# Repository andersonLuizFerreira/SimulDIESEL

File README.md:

# SimulDIESEL

---

# Português

O SimulDIESEL consiste em uma plataforma de bancada destinada à manutenção, diagnóstico, análise, simulação e validação de centrais e módulos automotivos da linha DIESEL, com foco em caminhões, máquinas agrícolas e equipamentos pesados.

Suas ferramentas permitem ao reparador realizar testes, simulações e análises de funcionamento de redes, sinais e módulos eletrônicos, auxiliando processos de manutenção, desenvolvimento, engenharia reversa e diagnóstico avançado em bancada.

Para conhecer mais sobre o projeto, leia:

- [`docs/README.md`](docs/README.md)
- [`docs/00-INDICE.md`](docs/00-INDICE.md)

Esses arquivos guiarão você pela documentação e estrutura do projeto.

## agentes de IA

Siga para:

- [`.agents/README.md`](.agents/README.md)

---

# English

SimulDIESEL is a bench platform designed for maintenance, diagnostics, analysis, simulation, and validation of DIESEL automotive control units and electronic modules, focused on trucks, agricultural machines, and heavy equipment.

Its tools allow technicians to perform tests, simulations, and analysis of networks, signals, and electronic modules, supporting maintenance, development, reverse engineering, and advanced bench diagnostics.

To learn more about the project, read:

- [`docs/README.md`](docs/README.md)
- [`docs/00-INDICE.md`](docs/00-INDICE.md)

These files will guide you through the project's documentation and structure.

## AI agents

Proceed to:

- [`.agents/README.md`](.agents/README.md)

---

# Español

SimulDIESEL es una plataforma de banco destinada al mantenimiento, diagnóstico, análisis, simulación y validación de centrales y módulos automotrices de la línea DIESEL, enfocada en camiones, maquinaria agrícola y equipos pesados.

Sus herramientas permiten al reparador realizar pruebas, simulaciones y análisis del funcionamiento de redes, señales y módulos electrónicos, ayudando en procesos de mantenimiento, desarrollo, ingeniería inversa y diagnóstico avanzado en banco.

Para conocer más sobre el proyecto, lea:

- [`docs/README.md`](docs/README.md)
- [`docs/00-INDICE.md`](docs/00-INDICE.md)

Estos archivos lo guiarán a través de la documentación y estructura del proyecto.

## agentes de IA

Diríjase a:

- [`.agents/README.md`](.agents/README.md)

---

# Deutsch

SimulDIESEL ist eine Prüfstandsplattform für Wartung, Diagnose, Analyse, Simulation und Validierung von Steuergeräten und elektronischen Modulen im DIESEL-Bereich mit Fokus auf Lastkraftwagen, landwirtschaftliche Maschinen und schwere Geräte.

Die Werkzeuge ermöglichen Technikern die Durchführung von Tests, Simulationen und Analysen von Netzwerken, Signalen und elektronischen Modulen und unterstützen Wartung, Entwicklung, Reverse Engineering und erweiterte Prüfstandsdiagnosen.

Um mehr über das Projekt zu erfahren, lesen Sie:

- [`docs/README.md`](docs/README.md)
- [`docs/00-INDICE.md`](docs/00-INDICE.md)

Diese Dateien führen Sie durch die Dokumentation und Struktur des Projekts.

## KI-Agenten

Weiter zu:

- [`.agents/README.md`](.agents/README.md)

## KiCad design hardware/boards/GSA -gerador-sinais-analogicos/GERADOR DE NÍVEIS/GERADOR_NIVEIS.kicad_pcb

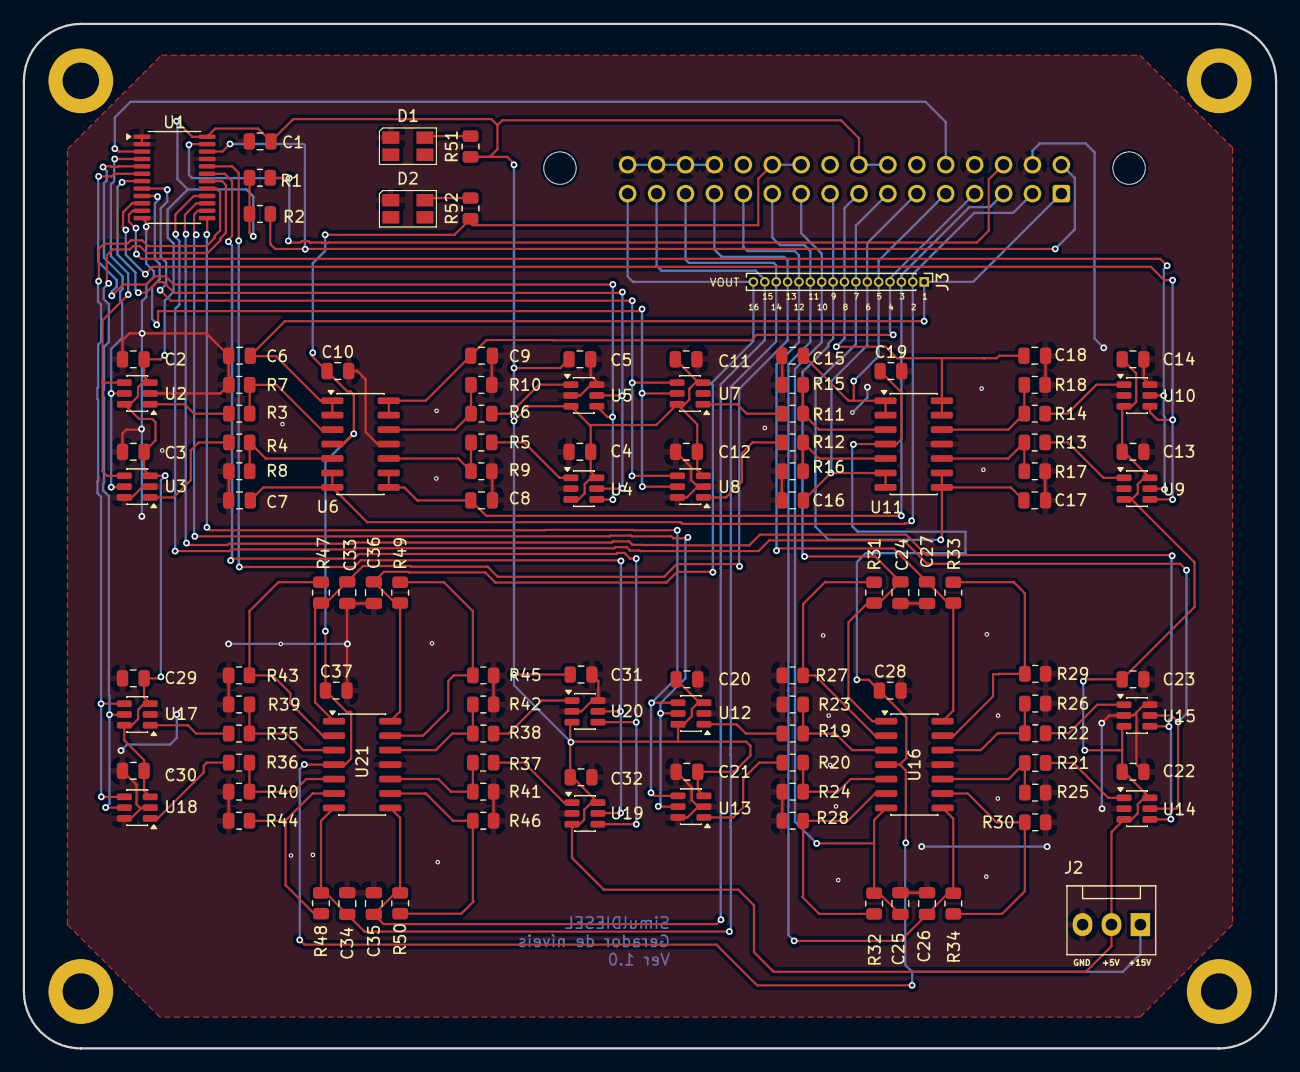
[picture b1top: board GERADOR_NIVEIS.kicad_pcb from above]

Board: 2 copper layers, 110.0 x 90.0 mm, 115 parts (1 on the bottom side), 80 nets.

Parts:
C1, C2, C3, C4, C5, C6, C7, C8, C9, C10, C11, C12, C13, C14, C15, C16, C17, C18, C19, C20, C21, C22, C23, C24, C25, C26, C27, C28, C29, C30, C31, C32, C33, C34, C35, C36, C37: 100nF; C_0805_2012Metric
D1, D2: LED; LED_Avago_PLCC4_3.2x2.8mm_CW
J1: DIN41612_02x16_AB; DIN41612_B2_2x16_Female_Vertical_THT
J2: Conn_01x03_Pin; FanPinHeader_1x03_P2.54mm_Vertical
J3: Conn_01x16_Pin; PinHeader_1x16_P1.00mm_Vertical
R1, R2: 4K7; R_0805_2012Metric
R3, R4, R5, R6, R11, R12, R13, R14, R19, R20, R21, R22, R35, R36, R37, R38, R51: 1K; R_0805_2012Metric
R7, R8, R9, R10, R15, R16, R17, R18, R23, R24, R25, R26, R39, R40, R41, R42: 100K; R_0805_2012Metric
R27, R28, R29, R30, R43, R44, R45, R46: 10K; R_0805_2012Metric
R31, R32, R33, R34, R47, R48, R49, R50: 15K; R_0805_2012Metric
R52: 3k3; R_0805_2012Metric
U1: TCA9548APWR; TSSOP-24_4.4x7.8mm_P0.65mm
U2, U3, U4, U5, U7, U8, U9, U10, U12, U13, U14, U15, U17, U18, U19, U20: MCP4725AOT; SOT-23-6
U6, U11, U16, U21: LM2902; SOIC-14_3.9x8.7mm_P1.27mm

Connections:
+15V: C10.1, C19.1, C28.1, C37.1, J1.b10, J1.b11, J2.1, R52.1, U6.4 (V+), U11.4 (V+), U16.4 (V+), U21.4 (V+)
/SC0: U1.5 (SC0), U2.5 (SCL), U3.5 (SCL)
/SC1: U1.7 (SC1), U4.5 (SCL), U5.5 (SCL)
/SC2: U1.9 (SC2), U7.5 (SCL), U8.5 (SCL)
/SC3: U1.11 (SC3), U9.5 (SCL), U10.5 (SCL)
/SC4: U1.14 (SC4), U12.5 (SCL), U13.5 (SCL)
/SC5: U1.16 (SC5), U14.5 (SCL), U15.5 (SCL)
/SC6: U1.18 (SC6), U17.5 (SCL), U18.5 (SCL)
/SC7: U1.20 (SC7), U19.5 (SCL), U20.5 (SCL)
/SCL: J1.b1, R2.2, U1.22 (SCL)
/SD0: U1.4 (SD0), U2.4 (SDA), U3.4 (SDA)
/SD1: U1.6 (SD1), U4.4 (SDA), U5.4 (SDA)
/SD2: U1.8 (SD2), U7.4 (SDA), U8.4 (SDA)
/SD3: U1.10 (SD3), U9.4 (SDA), U10.4 (SDA)
/SD4: U1.13 (SD4), U12.4 (SDA), U13.4 (SDA)
/SD5: U1.15 (SD5), U14.4 (SDA), U15.4 (SDA)
/SD6: U1.17 (SD6), U17.4 (SDA), U18.4 (SDA)
/SD7: U1.19 (SD7), U19.4 (SDA), U20.4 (SDA)
/SDA: J1.b3, R1.2, U1.23 (SDA)
/VOUT1: C6.1, J1.a1, J3.1, U6.1, U6.2 (-)
/VOUT2: C7.1, J1.a2, J3.2, U6.6 (-), U6.7
/VOUT3: C8.1, J1.a3, J3.3, U6.8, U6.9 (-)
/VOUT4: C9.1, J1.a4, J3.4, U6.13 (-), U6.14
/VOUT5: C15.1, J1.a5, J3.5, U11.1, U11.2 (-)
/VOUT6: C16.1, J1.a6, J3.6, U11.6 (-), U11.7
/VOUT7: C17.1, J1.a7, J3.7, U11.8, U11.9 (-)
/VOUT8: C18.1, J1.a8, J3.8, U11.13 (-), U11.14
/VOUT9: C24.1, J1.a9, J3.9, R31.2, U16.1
/VOUT10: C25.1, J1.a10, J3.10, R32.2, U16.7
/VOUT11: C26.1, J1.a11, J3.11, R34.2, U16.8
/VOUT12: C27.1, J1.a12, J3.12, R33.2, U16.14
/VOUT13: C33.1, J1.a13, J3.13, R47.2, U21.1
/VOUT14: C34.1, J1.a14, J3.14, R48.2, U21.7
/VOUT15: C35.1, J1.a15, J3.15, R50.2, U21.8
/VOUT16: C36.1, J1.a16, J3.16, R49.2, U21.14
/~RST: J1.b5, U1.3 (~RESET)
GND: C1.1, C2.2, C3.2, C4.2, C5.2, C6.2, C7.2, C8.2, C9.2, C10.2, C11.2, C12.2, C13.2, C14.2, C15.2, C16.2, C17.2, C18.2, C19.2, C20.2, C21.2, C22.2, C23.2, C24.2, C25.2, C26.2, C27.2, C28.2, C29.2, C30.2, C31.2, C32.2, C33.2, C34.2, C35.2, C36.2, C37.2, D1.1 (K), D2.1 (K), J1.b2, J1.b4, J1.b13, J1.b14, J1.b15, J1.b16, J2.3, R7.1, R8.1, R9.1, R10.1, R15.1, R16.1, R17.1, R18.1, R23.1, R24.1, R25.1, R26.1, R27.1, R28.1, R29.1, R30.1, R39.1, R40.1, R41.1, R42.1, R43.1, R44.1, R45.1, R46.1, U1.1 (A0), U1.2 (A1), U1.12 (GND), U1.21 (A2), U2.2 (VSS), U3.2 (VSS), U3.6 (A0), U4.2 (VSS), U5.2 (VSS), U5.6 (A0), U6.11 (V-), U7.2 (VSS), U8.2 (VSS), U8.6 (A0), U9.2 (VSS), U10.2 (VSS), U10.6 (A0), U11.11 (V-), U12.2 (VSS), U13.2 (VSS), U13.6 (A0), U14.2 (VSS), U15.2 (VSS), U15.6 (A0), U16.11 (V-), U17.2 (VSS), U18.2 (VSS), U18.6 (A0), U19.2 (VSS), U20.2 (VSS), U20.6 (A0), U21.11 (V-)
unnamed: D1.2 (A), R51.2
unnamed: D2.2 (A), R52.2
unnamed: R3.1, U2.1 (VOUT)
unnamed: R4.1, U3.1 (VOUT)
unnamed: R5.1, U4.1 (VOUT)
unnamed: R6.1, U5.1 (VOUT)
unnamed: R3.2, R7.2, U6.3 (+)
unnamed: R4.2, R8.2, U6.5 (+)
unnamed: R5.2, R9.2, U6.10 (+)
unnamed: R6.2, R10.2, U6.12 (+)
unnamed: R11.1, U7.1 (VOUT)
unnamed: R12.1, U8.1 (VOUT)
unnamed: R13.1, U9.1 (VOUT)
unnamed: R14.1, U10.1 (VOUT)
unnamed: R11.2, R15.2, U11.3 (+)
unnamed: R12.2, R16.2, U11.5 (+)
unnamed: R13.2, R17.2, U11.10 (+)
unnamed: R14.2, R18.2, U11.12 (+)
unnamed: R19.1, U12.1 (VOUT)
unnamed: R20.1, U13.1 (VOUT)
unnamed: R21.1, U14.1 (VOUT)
unnamed: R22.1, U15.1 (VOUT)
unnamed: R19.2, R23.2, U16.3 (+)
unnamed: R27.2, R31.1, U16.2 (-)
unnamed: R20.2, R24.2, U16.5 (+)
unnamed: R28.2, R32.1, U16.6 (-)
unnamed: R21.2, R25.2, U16.10 (+)
unnamed: R30.2, R34.1, U16.9 (-)
unnamed: R22.2, R26.2, U16.12 (+)
unnamed: R29.2, R33.1, U16.13 (-)
unnamed: R35.1, U17.1 (VOUT)
unnamed: R36.1, U18.1 (VOUT)
unnamed: R37.1, U19.1 (VOUT)
unnamed: R38.1, U20.1 (VOUT)
unnamed: R35.2, R39.2, U21.3 (+)
unnamed: R43.2, R47.1, U21.2 (-)
unnamed: R36.2, R40.2, U21.5 (+)
unnamed: R44.2, R48.1, U21.6 (-)
unnamed: R37.2, R41.2, U21.10 (+)
unnamed: R46.2, R50.1, U21.9 (-)
unnamed: R38.2, R42.2, U21.12 (+)
unnamed: R45.2, R49.1, U21.13 (-)
VCC: C1.2, C2.1, C3.1, C4.1, C5.1, C11.1, C12.1, C13.1, C14.1, C20.1, C21.1, C22.1, C23.1, C29.1, C30.1, C31.1, C32.1, J1.b7, J1.b8, J2.2, R1.1, R2.1, R51.1, U1.24 (VCC), U2.3 (VDD), U2.6 (A0), U3.3 (VDD), U4.3 (VDD), U4.6 (A0), U5.3 (VDD), U7.3 (VDD), U7.6 (A0), U8.3 (VDD), U9.3 (VDD), U9.6 (A0), U10.3 (VDD), U12.3 (VDD), U12.6 (A0), U13.3 (VDD), U14.3 (VDD), U14.6 (A0), U15.3 (VDD), U17.3 (VDD), U17.6 (A0), U18.3 (VDD), U19.3 (VDD), U19.6 (A0), U20.3 (VDD)

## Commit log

2026-02-01 Estruturação das pastas
2026-02-02 docs(protocol): add SD-GW-LINK spec, ADR-0007 and hex test vectors
2026-02-06 Atualização da documentação do protocolo SGGW
2026-02-09 Conexão serial pronta.
2026-02-09 docs: add architecture overview, serial baseline and technical roadmap
2026-02-09 feat: add link handshake...
2026-02-10 Inclusão do novo script git
2026-02-10 Novo script git
2026-02-10 Alteracao no script git
2026-02-10 Alteracoes no scritp do gitlab
2026-02-10 Tratamento de link
2026-02-13 SGGW em desenvolvimento
2026-02-14 Implement stable link handshake, health supervision, and graceful disconnect
2026-02-17 Integrate SGGW: link engine + client API + LED tool + ESP32 firmware
2026-02-21 gateway: reorganiza estrutura para modelo src/ + roteamento TLV puro
2026-02-21 ci: adiciona pipeline placeholder (YAML válido)
2026-02-28 Reestrutura docs e firmware (nova arvore)
2026-02-28 Adiciona CI para firmware (PlatformIO)
2026-02-28 Padroniza estrutura de docs (INDEX, duplicados e Master Spec)
2026-02-28 Adiciona relatório de auditoria estrutural
2026-02-28 Docs: restaura ADR-0007 (COBS + CRC-8)
2026-02-28 Docs: transforma README em HUB técnico
2026-02-28 Docs: adiciona MASTER_SPEC consolidado
2026-02-28 Docs: remove duplicidade de README (SGGW_OVERVIEW, EXAMPLES)
2026-02-28 Docs: ignore auditoria gerada (AUDITORIA_DOCS.md)
2026-02-28 Chore: move relatórios gerados para tools/out e ignora a pasta
2026-03-01 Docs(GSA): adiciona documentação base do firmware (README, protocolo, pinout, fluxo)
2026-03-01 Docs: remove specs do README e normaliza UTF-8
2026-03-01 docs(sggw): freeze SGGW v1.0 (name + ACK/ERR + boundaries)
2026-03-01 docs: add AI workflow + codex instructions
2026-03-06 SimulDIESEL v0.3.0
    Arquitetura estabilizada
    Reorganização completa da documentação
    Separação arquitetura / hardware
    Integração PC ↔ Gateway definida
    Estrutura do projeto consolidada
2026-03-14 docs: restore and sanitize documentation structure
2026-03-14 git: normalize line endings policy
2026-03-14 docs: update documentation and project state
2026-03-16 Fix I2C instability, restore stable BPM/GSA modules, and validate GSA LED command end-to-end
2026-03-17 Refatora arquitetura do local-api por boards, forms logic e camadas de protocolo
2026-03-17 Remove dump técnico da refatoração
2026-03-17 Ajusta regras de EOL no repositório
2026-03-18 docs: atualiza arquitetura oficial host <-> BPM, remove topologia legacy e alinha keepalive por atividade SDGW válida
2026-03-18 refactor: centraliza TX SDGW com scheduler por prioridade, substitui health service por link supervisor e alinha BPM ao keepalive por atividade válida
2026-03-22 Checkpoint antes da implementação completa da GSA
2026-03-22 Implementa expansão SDH/TLV da GSA no host
2026-03-22 Atualiza documentação da GSA e do contrato SDH/TLV
2026-03-22 Remove legados e consolida arquitetura atual da GSA
2026-03-22 Checkpoint antes da migração do TLV 0x12 para 0x1B na GSA
2026-03-22 Migra GSA channel.status de 0x12 para 0x1B
2026-03-22 Checkpoint antes da implementação do firmware GSA com simulação analógica e EEPROM
2026-03-22 Checkpoint antes da implementação I2C real TCA9548 + MCP4725
2026-03-22 Checkpoint antes da implementação da máquina operacional GSA BUSY/IDLE + I2C master/slave + TCA9548 + MCP4725
2026-03-22 Checkpoint antes da integração da UI da GSA com comandos reais
2026-03-24 Checkpoint antes da adaptação do gateway BPM para IRQ + evento 0x31 da GSA
2026-03-24 Checkpoint antes da integração I2C duplo + IRQ + evento 0x31 na GSA
2026-03-24 Checkpoint antes da atualização documental da nova arquitetura GSA/BPM/API
2026-03-24 Checkpoint antes da adaptação da API/UI ao evento 0x31 da GSA
2026-03-27 Checkpoint antes da Fase 1 - refatoracao do host para multiplos transportes
2026-03-27 Refatora host SDGW para desacoplar sessao do transporte e preservar Serial
2026-03-27 Checkpoint antes da Fase 2 - refatoracao do firmware BPM para multiplos transportes
2026-03-27 Refatora firmware BPM para desacoplar SGGW do stream fisico e preservar Serial
2026-03-27 Checkpoint antes da Fase 3 - implementacao Bluetooth host e firmware BPM
2026-03-27 Implementa Bluetooth no host e na BPM com sessao unica e Serial preservada
2026-04-03 Correção definitiva da pinagem BPM-GSA e saneamento global do projeto
2026-04-03 Checkpoint antes da reestruturacao da documentacao
2026-04-05 docs: consolida a árvore oficial da documentação
    Reestrutura a navegação hierárquica, ajusta a conformidade entre pai e filho e organiza a leitura progressiva por camadas.
2026-04-06 docs: aprofunda documentação de firmware e hardware e fecha etapa atual
    Reflete o estado implementado de BPM, GSA e da bancada, consolida as trilhas ONDE e COMO fora da API e registra o fechamento da etapa atual, deixando apenas a finalização da GSA pendente e preparando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
2026-04-06 refactor: consolida nova fundação SDGW e estrutura modular da solução
2026-04-12 feat: comissionamento final e documentacao da UCE
2026-04-17 Checkpoint SPI Parte A: correção do transporte BPM<->UCE com TX explícito no slave, validação de header no master e melhoria na classificação de erros. Builds OK (UCE/BPM). Validação em bancada pende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
2026-04-17 Checkpoint SPI Parte A + comissionamento: correção do transporte BPM<->UCE, dumps técnicos versionados para rastreabilidade, builds OK, validação de bancada pendente
2026-04-24 Commission validated BPM-UCE SPI LED handshake
2026-04-25 feat: comissiona transporte SPI e dispatchers por board
2026-04-25 refactor: centraliza transacoes TLV por board na API
2026-04-25 feat(uce): adiciona CanService logico (0x20-0x23) integrado com dispatcher e API
2026-04-25 Desenvolvendo controle de mensagens CAN
2026-04-27 feat(can): implementa CAN_RX_EVENT assíncrono com pipeline UCE→BPM→API validado em bancada
2026-04-30 Construção de CanService na UCE
2026-04-30 Implantacao da CanService
2026-05-02 Continuação da construção do canService
2026-05-08 feat(can-rx): consolida arquitetura RX AUTO/DIRECT_ONLY com TIC, DATA_MASK e OutputBuffer
    Consolida a ETAPA 10 do fluxo CAN RX com CAN_TIC 0x46, CAN_EDIT otimizado por DATA_MASK e replay oficial via CanRxOutputBuffer.
    Preserva DIRECT_ONLY e CAN_RX_EVENT 0x28, mantém fallback TABLE_FULL, DELETE por timeout, recuperação MIRROR_OUT_OF_SYNC e diagnóstico de FIFO dispatcher.
    Inclui cenários controlados no CanDriver_fake para TIC sem alteração, EDIT com um byte alterado e DELETE por timeout, sem alterar CanDriver real.
2026-05-08 feat(can-tx): valida arquitetura TX DIRECT/TABLE com loopback fake RX/TX
    - implementa CAN_TX_DIRECT/TX_CREATE/TX_EDIT/TX_DELETE
    - adiciona tabela TX na UCE
    - adiciona CanTxManager na API
    - valida loopback TX->RX via CanDriver_fake
    - valida DIRECT_ONLY vs AUTO
    - consolida arquitetura RX/TX da ETAPA 10
2026-05-09 feat(sdctp): consolida arquitetura final CAN transport protocol para producao
2026-05-09 feat(api): inicia camada de decodificacao J1939
2026-05-09 feat(api): inicia bloco protocolar J1939 encapsulado
2026-05-09 feat(api): implementa camada data link J1939-21
2026-05-09 feat(api): implementa camada application J1939-71 inicial
2026-05-09 feat(api): implementa diagnostico J1939-73 inicial com leitura DM1 DM2
2026-05-09 chore(api): remove log legado de depuracao CAN_TIC
2026-05-09 feat(api): implementa network management J1939-81 inicial
2026-05-09 feat(api): adiciona catalogo padrao de PGNs J1939
2026-05-11 Conclusão do J1939
2026-05-11 Separação de protocolos
2026-05-12 ETAPA: Consolidação da estrutura AGENTS/Skills + início da aplicação Rede CAN
    Consolida AGENTS.md, docs/agents, skills estruturadas em .codex, dumps de ETAPA e padronização SDCTP.
    Inclui também os recursos visuais e botão inicial da Rede CAN no Dashboard.
2026-05-12 ETAPA Banco Local: consolidacao da infraestrutura SQLite + BD_Service_Provider + CRUD piloto ModuleProfile
2026-05-12 Fim da implantação do BD
2026-05-13 Implantacao da Rede CAN
2026-05-16 chore: ajusta governanca git e remove artefatos runtime do versionamento
2026-05-17 docs: cria guia comum para agentes
2026-05-17 chore: remove scripts bat obsoletos da raiz
2026-05-17 docs: consolida bootstrap de agentes em .agents
2026-05-17 docs: rebaixa AGENTS.md para redirecionamento
2026-05-17 docs: absorve governanca do AGENTS em .agents
2026-05-17 docs: remove AGENTS legado apos migracao para .agents
2026-05-17 docs: migra indice de skills para .agents
2026-05-17 docs: consolida .agents como governanca unica
2026-05-17 docs: cria README raiz como roteador universal
2026-05-17 docs: simplifica bootstrap de agentes no README raiz
2026-05-17 docs: transforma .agents README em roteador central
2026-05-17 docs: refina onboarding humano e agentes no README
2026-05-17 docs: adiciona README multilíngue com acentuação correta
2026-05-17 Update section headers for AI agents in README
2026-05-17 docs: consolida instructions no README da governanca
2026-05-17 docs: remove instructions apos consolidacao no README
2026-05-17 docs: migra skill de arquitetura para .agents
2026-05-17 docs: migra skill architecture para .agents
2026-05-17 docs: migra skill winforms-ui para .agents
2026-05-17 docs: migra skill bll-dal-dtl para .agents
2026-05-17 docs: centraliza regras globais de agentes
2026-05-17 docs: consolida governanca de agentes e saneia skills
2026-05-17 docs: adiciona skill de gestao de regras de governanca
2026-05-17 implantação da governaça do projeto
2026-05-17 docs: reforca regra de gestao de governanca IA
2026-05-17 docs: reforca autoridade e hierarquia da governanca
2026-05-17 docs: atualiza skill de governanca
2026-05-17 docs: adiciona skill de workflow de execucao de tarefas
2026-05-17 docs: adiciona workflow oficial de execucao de tarefas
2026-05-17 docs: ajusta selecao padrao de tarefas pendentes
2026-05-17 docs: restaura README global completo com workflow operacional
2026-05-17 docs: centraliza regras especificas de tasks na skill local
2026-05-17 docs: reduz detalhes operacionais do workflow no README global
2026-05-17 docs: adiciona skill de governanca documental
2026-05-17 docs: reforca regras da governanca documental
2026-05-18 docs: ajusta regra transitoria de divergencia docs x codigo
2026-05-18 docs: absorve regras antigas de DOCUMENTATION_RULES para skill docs
2026-05-18 Delete official nomenclature section
    Remove official nomenclature section from SKILL.md
2026-05-18 docs: cria primeira ETAPA de saneamento documental
2026-05-18 Specify output path for task reports
    Add output path for task reports in documentation.
2026-05-18 Audit documentation governance
2026-05-18 Record documentation audit commit
2026-05-18 docs: cria ETAPA de consolidacao estrutural de docs
2026-05-18 Consolidate documentation structure
2026-05-18 Record documentation consolidation commit
2026-05-18 docs: cria ETAPA de atualizacao documental baseada no codigo
2026-05-18 Update docs from code state
2026-05-18 Record docs update execution hash
2026-05-18 Atualização de docs
2026-05-18 docs: formaliza estilo editorial humano em docs-governance
2026-05-18 docs: melhora README da documentacao oficial
2026-05-18 docs: humaniza visao geral do projeto
2026-05-18 docs: melhora visao arquitetural
2026-05-19 docs: refatora visao fisica do projeto
2026-05-19 docs: refatora api e host local
2026-05-19 docs: refatora visao fisica da bll do host
2026-05-19 docs: refatora visao fisica da dal do host
2026-05-19 docs: refatora visao fisica da dtl do host
